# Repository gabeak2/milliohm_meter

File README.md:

# milliohm_meter
A milliohm meter PCBA reading 10V/Ohm, designed to be powered off of a RCR123A battery.  It plugs directly into standard DVMs with 2 male banana pins with 19mm spacing, and uses kelvin sensing for resistance readings.

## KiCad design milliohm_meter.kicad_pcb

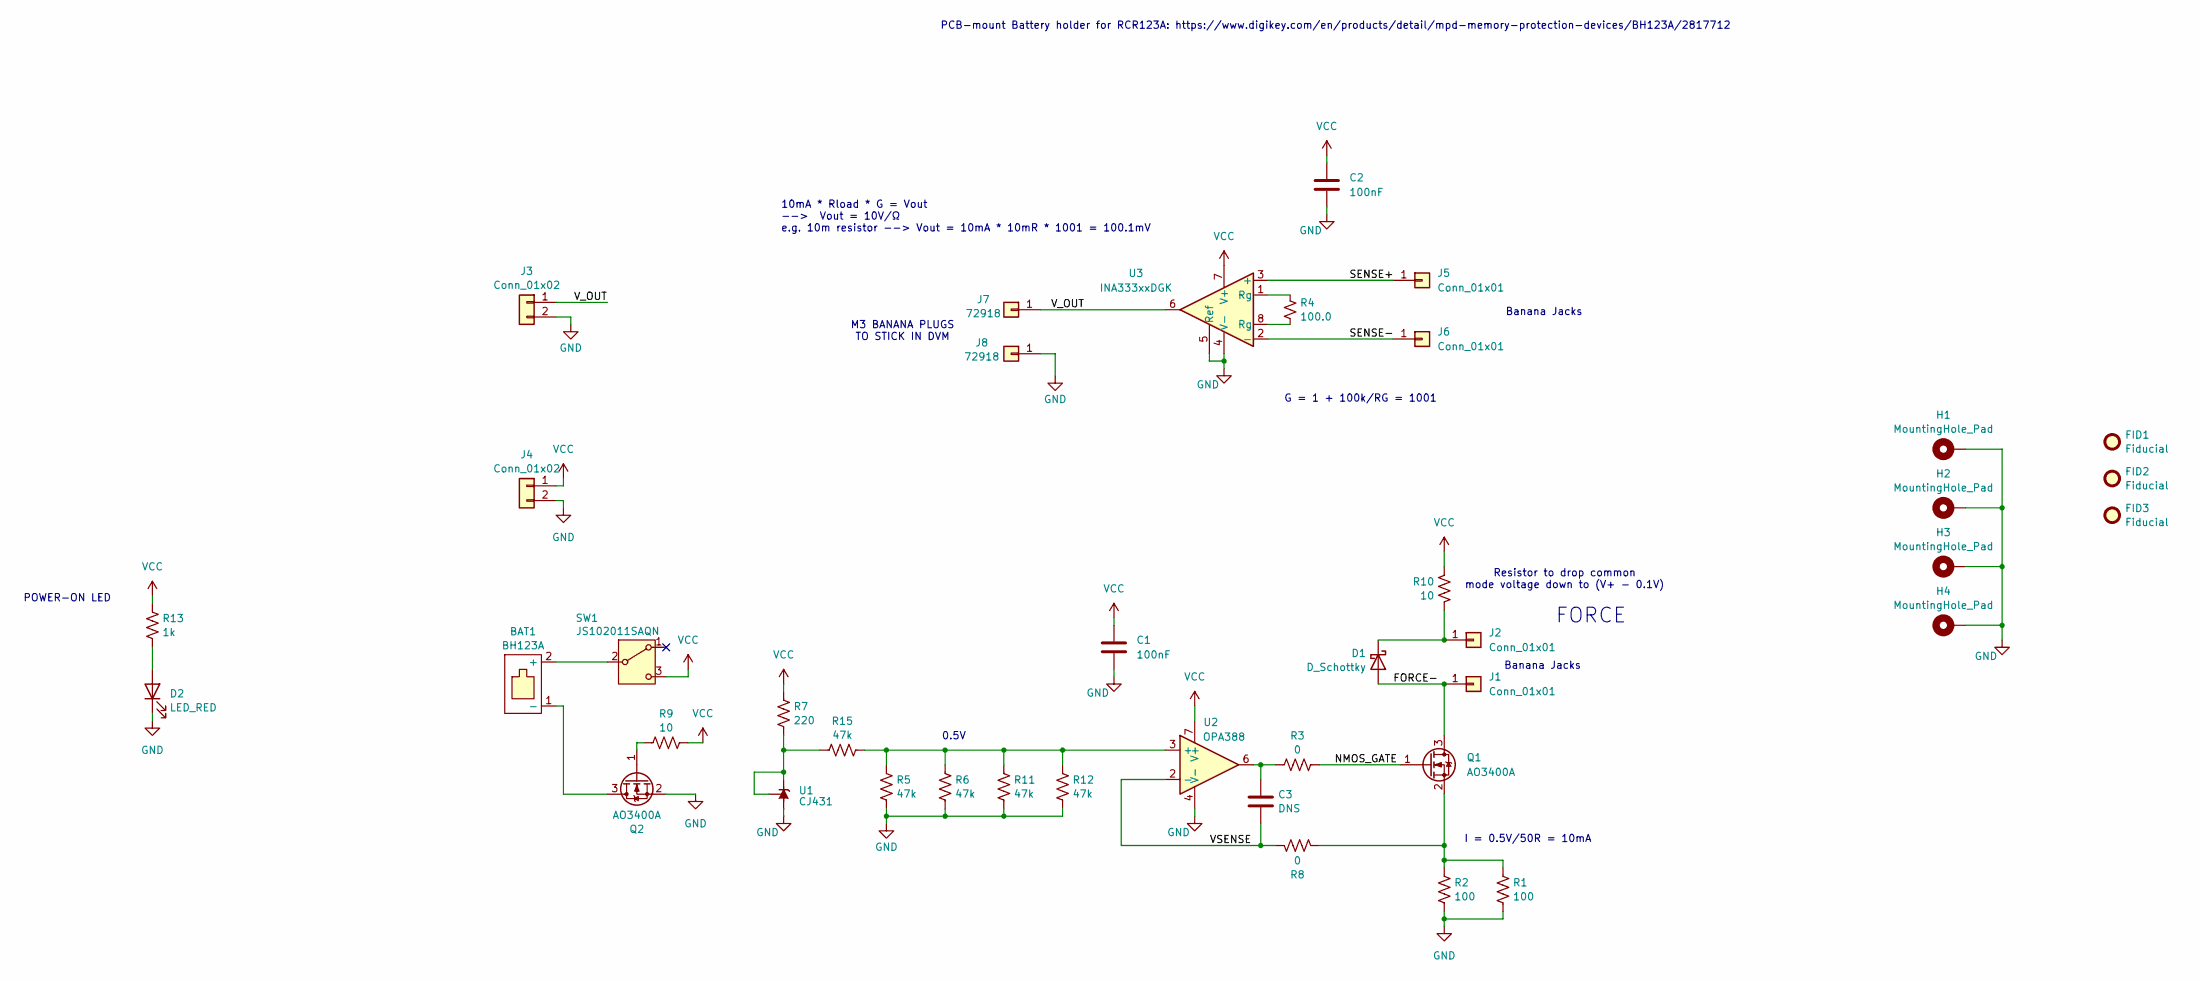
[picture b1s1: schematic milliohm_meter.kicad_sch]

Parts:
BAT1: BH123A
C1, C2: 100nF; C_0402_1005Metric; LCSC C307331
C3: DNS; C_0402_1005Metric
D1: D_Schottky; D_SOD-323; LCSC C191023
D2: LED_RED; LED_0805_2012Metric; LCSC C84256
FID1, FID2, FID3: Fiducial; Fiducial_1mm_Mask2mm
H1, H2, H3, H4: MountingHole_Pad; MountingHole_3.2mm_M3_Pad
J1, J2, J5, J6: Conn_01x01; CT3149
J3, J4: Conn_01x02; PinSocket_1x02_P2.54mm_Vertical
J7, J8: 72918; MountingHole_3.2mm_M3_Pad
Q1, Q2: AO3400A; SOT-23; LCSC C20917
R1, R2: 100; C_0402_1005Metric; LCSC C705656
R3, R8: 0; R_0402_1005Metric; LCSC C17168
R4: 100.0; C_0402_1005Metric; LCSC C705656
R5, R6, R11, R12, R15: 47k; C_0402_1005Metric; LCSC C358418
R7: 220; C_0402_1005Metric; LCSC C25091
R9, R10: 10; C_0402_1005Metric; LCSC C25077
R13: 1k; C_0402_1005Metric; LCSC C11702
SW1: JS102011SAQN; SW_SPDT_CK_JS102011SAQN; LCSC C221660
U1: CJ431; SOT-23; LCSC C3113
U2: OPA388; SOIC-8_3.9x4.9mm_P1.27mm; LCSC C154118
U3: INA333xxDGK; VSSOP-8_3.0x3.0mm_P0.65mm; LCSC C19450

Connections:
/FORCE-: D1.2 (A), J1.1, Q1.3 (D)
/NMOS_GATE: Q1.1 (G), R3.1
/SENSE+: J5.1, U3.3 (+)
/SENSE-: J6.1, U3.2 (-)
/VSENSE: C3.2, R8.2, U2.2 (-)
/V_OUT: J3.1, J7.1, U3.6
GND: C1.2, C2.2, D2.1 (K), H1.1, H2.1, H3.1, H4.1, J3.2, J4.2, J8.1, Q2.2 (S), R1.2, R2.2, R5.1, R6.1, R11.1, R12.1, U1.3 (A), U2.4 (V-), U3.4 (V-), U3.5 (Ref)
unnamed: BAT1.2 (+), SW1.2 (B)
unnamed: BAT1.1 (-), Q2.3 (D)
unnamed: C3.1, R3.2, U2.6
unnamed: D1.1 (K), J2.1, R10.2
unnamed: D2.2 (A), R13.1
unnamed: Q1.2 (S), R1.1, R2.1, R8.1
unnamed: Q2.1 (G), R9.1
unnamed: R4.1, U3.1 (Rg)
unnamed: R4.2, U3.8 (Rg)
unnamed: R7.2, R15.1, U1.1 (REF), U1.2 (K)
unnamed: R5.2, R6.2, R11.2, R12.2, R15.2, U2.3 (+)
VCC: C1.1, C2.1, J4.1, R7.1, R9.2, R10.1, R13.2, SW1.3 (C), U2.7 (V+), U3.7 (V+)

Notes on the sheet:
Resistor to drop common mode voltage down to (V+ - 0.1V)
POWER-ON LED
0.5V
M3 BANANA PLUGS TO STICK IN DVM
I = 0.5V/50R = 10mA
FORCE
10mA * Rload * G = Vout --> Vout = 10V/Ω e.g. 10m resistor --> Vout = 10mA * 10mR * 1001 = 100.1mV
Banana Jacks
G = 1 + 100k/RG = 1001
PCB-mount Battery holder for RCR123A: https://www.digikey.com/en/products/detail/mpd-memory-protection-devices/BH123A/2817712

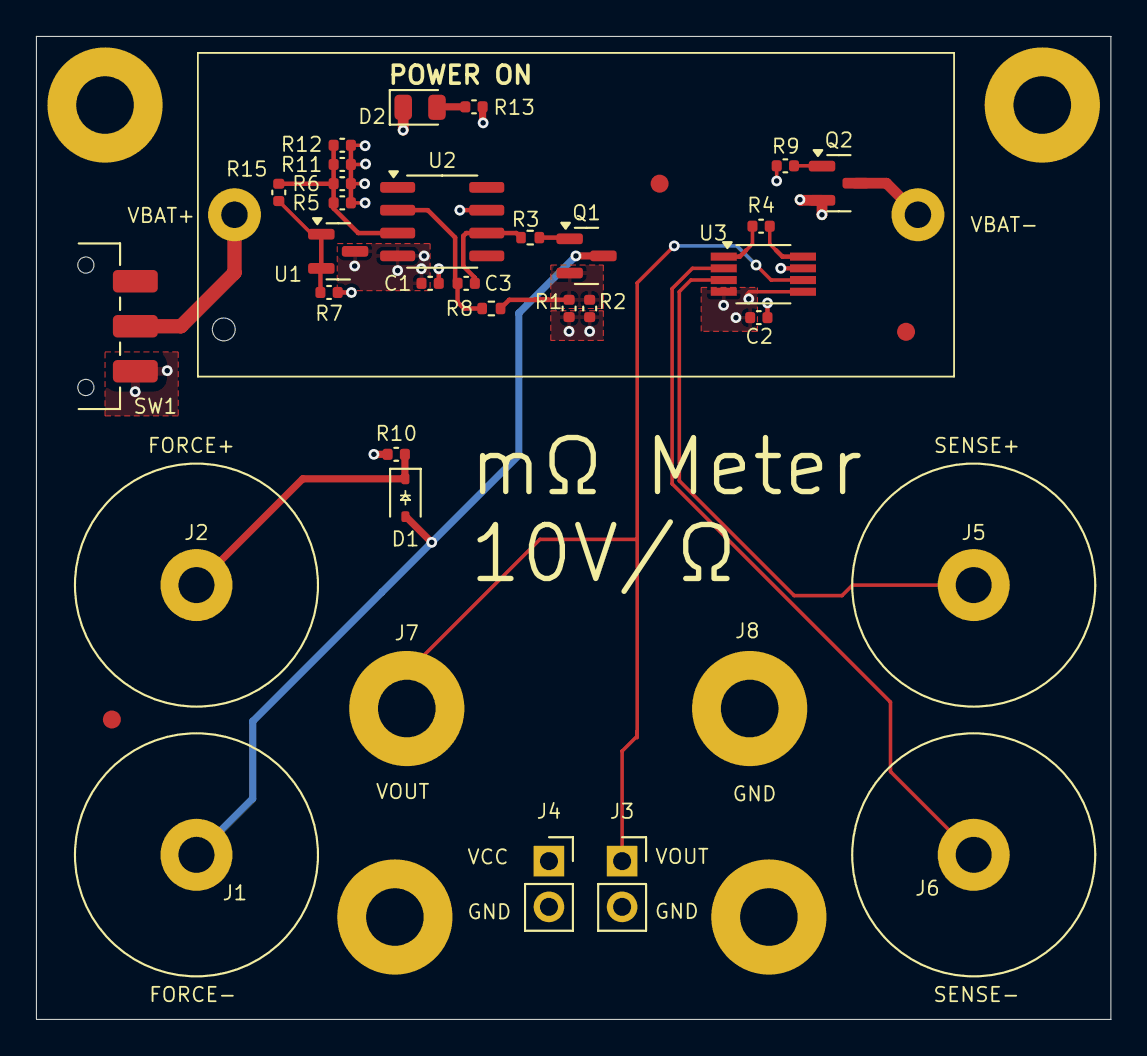
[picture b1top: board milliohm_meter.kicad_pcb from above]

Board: 4 copper layers, 59.7 x 54.6 mm, 41 parts (1 on the bottom side), 19 nets.

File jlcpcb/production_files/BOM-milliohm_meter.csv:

Comment,Designator,Footprint,LCSC
1k,R13,C_0402_1005Metric,C11702
OPA388,U2,SOIC-8_3.9x4.9mm_P1.27mm,C154118
0,"R3,R8",R_0402_1005Metric,C17168
D_Schottky,D1,D_SOD-323,C191023
INA333xxDGK,U3,VSSOP-8_3.0x3.0mm_P0.65mm,C19450
AO3400A,"Q1,Q2",SOT-23,C20917
JS102011SAQN,SW1,SW_SPDT_CK_JS102011SAQN,C221660
10,"R10,R9",C_0402_1005Metric,C25077
220,R7,C_0402_1005Metric,C25091
100nF,"C1,C2",C_0402_1005Metric,C307331
CJ431,U1,SOT-23,C3113
47k,"R11,R12,R15,R5,R6",C_0402_1005Metric,C358418
100,"R1,R2,R4",C_0402_1005Metric,C705656
LED_RED,D2,LED_0805_2012Metric,C84256
72918,J8,MountingHole_3.2mm_M3_Pad,
Conn_01x01,J2,CT3149,
Conn_01x02,J3,PinSocket_1x02_P2.54mm_Vertical,
DNS,C3,C_0402_1005Metric,
Conn_01x01,J6,CT3149,
Conn_01x02,J4,PinSocket_1x02_P2.54mm_Vertical,
72918,J7,MountingHole_3.2mm_M3_Pad,
Conn_01x01,J5,CT3149,
Conn_01x01,J1,CT3149,
BH123A,BAT1,BH123A,
